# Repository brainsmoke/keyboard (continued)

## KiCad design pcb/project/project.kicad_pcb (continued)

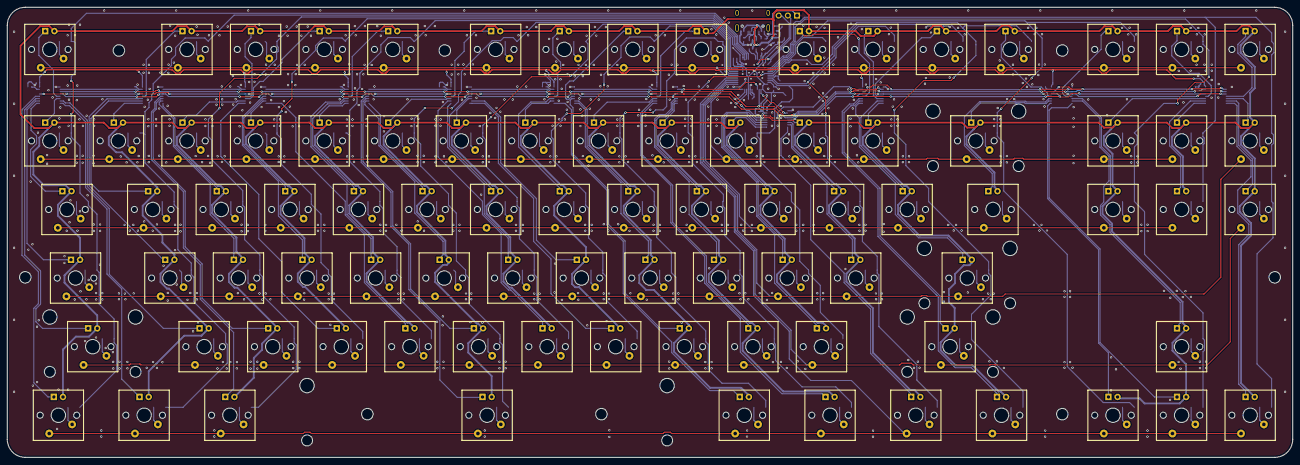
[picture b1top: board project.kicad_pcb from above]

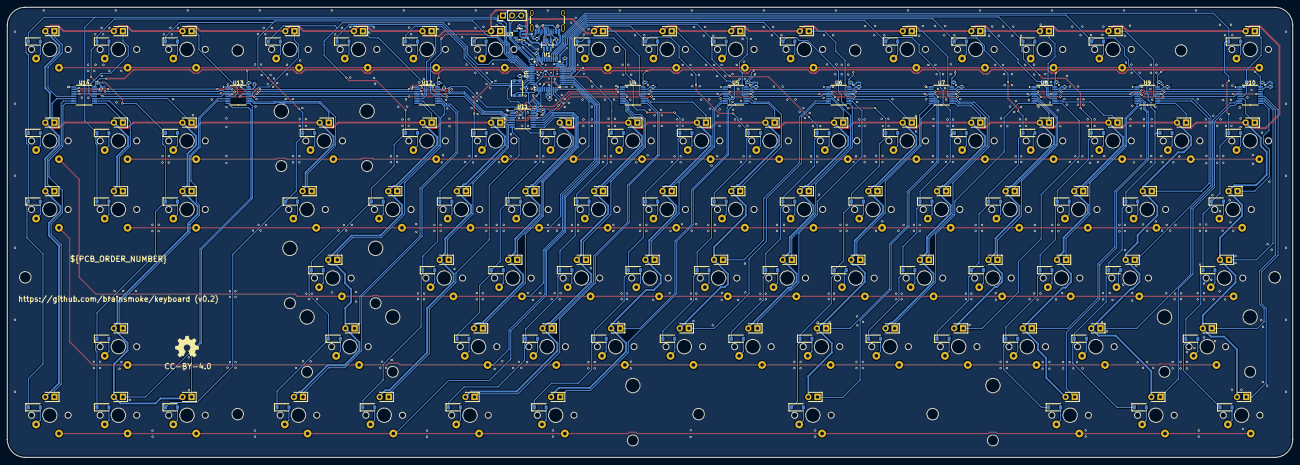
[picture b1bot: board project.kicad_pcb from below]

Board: 2 copper layers, 357.0 x 125.0 mm, 310 parts (223 on the bottom side), 234 nets.

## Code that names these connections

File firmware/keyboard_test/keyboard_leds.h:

#ifndef BITBANG_H
#define BITBANG_H

/* platform constants */

#define GPIO_ODR_OFFSET (0x14)
#define GPIO_BSRR_OFFSET (0x18)
#define GPIO_BRR_OFFSET (0x28)

/* GPIO, BSRR */

#define CLEAR(X) (X<<16)
#define SET(X)   (X)

/* GPIO C */
#define PIN_DATA_LEFT          (15)
#define PIN_DATA_RIGHT         (13)
#define PIN_CLK                (14)

/* GPIO A */
#define PIN_LATCH              (0)
#define PIN_NOT_OUTPUT_ENABLE  (1)


#define BIT_DATA_LEFT          (1<<PIN_DATA_LEFT)
#define BIT_DATA_RIGHT         (1<<PIN_DATA_RIGHT)
#define BIT_CLK                (1<<PIN_CLK)
#define BIT_LATCH              (1<<PIN_LATCH)
#define BIT_NOT_OUTPUT_ENABLE  (1<<PIN_NOT_OUTPUT_ENABLE)

#define MASK_CLK (BIT_CLK)
#define MASK_DATA (BIT_DATA_LEFT|BIT_DATA_RIGHT)

#ifndef __ASSEMBLER__

#include <stdint.h>
#include "config.h"

#define GPIO_LEDS_DATA (GPIOC)
#define GPIO_LEDS_LATCH (GPIOA)

#define BUFFER_BIT_DATA_LEFT (BIT_DATA_LEFT>>8)
#define BUFFER_BIT_DATA_RIGHT (BIT_DATA_RIGHT>>8)


#define MAX_BITS_PER_CHANNEL (56)
#define CHANNEL_PINS { BIT_DATA_LEFT, BIT_DATA_RIGHT, 0 }
#define CHANNEL_SIZES { 56, 32, 0 }

/* sends 56x bits parallel at 1/8th the clockspeed
 * gpio is the GPIO base address
 * 
 * probably close to 500 cycles including call
 */
void bitbang_56bits_stm32(uint8_t *buffer, volatile uint32_t *gpio_data_clock, volatile uint32_t *gpio_latch_enable, uint32_t not_enable_mask);
void write_wait_write(volatile uint32_t *addr, uint32_t pre_data, uint32_t post_data, uint32_t cycles);

#endif

#endif // BITBANG_H

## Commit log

2025-05-30 generate schematic
2025-05-31 board positioning
2025-05-31 put generator in scripts dir
2025-06-01 blagh
2025-06-07 routing done
2025-06-07 make external dimensions metric
2025-06-07 add build files
2025-06-07 add readme
2025-06-19 fixed the slots in the USB-C footprint, no clue how they got changed
2025-06-25 add measurement to keyboard key 'origin'
2025-06-25 add libopencm3 submodule
2025-06-25 copy common dir from usb_proto
2025-06-25 move files around
2025-06-25 test program
2025-06-26 reorg pcb/schematice generator scripts
2025-06-26 remove old file
2025-06-26 oops, missing file
2025-06-26 initial led driver code
2025-06-27 add header gen
2025-06-27 backlight test
2025-06-27 reshuffle
2025-06-27 clean up leds test
2025-06-28 rename binary
2025-06-30 test keyboard matrix hardware
2025-06-30 rename sheet labels to port names
2025-07-01 make key scanning slightly faster
2025-07-01 fix debug messgage
2025-07-17 add codegen scripts
2025-07-17 add distance calculation
2025-07-17 add codegen code
2026-02-15 rename headers
2026-02-15 add gitignore
2026-02-15 add footprints
2026-02-15 improve .gitignore
2026-02-15 add n-key rollover descriptor
2026-02-18 whitespace
2026-02-18 fix unfinished code to support unassigned keys
2026-02-25 working basic keyboard
2026-02-26 fix led mapping
2026-02-26 implement keyboard control protocol
2026-02-26 fix backlight
2026-02-26 add swapfn option to config.h
2026-02-26 fix led distance table
2026-03-01 implement set_idle ( untested :-E )
2026-03-01 don't send unneeded updates when fn is pressed
2026-03-04 save some RAM
2026-03-12 correct copyright date
2026-03-12 implement usb_hid_keyboard_key_is_down
2026-03-12 move/unify backlight leds bitbang routine
2026-03-12 remove unused files
2026-03-12 remove unused includes
2026-03-12 reorder functions for readability
2026-03-21 add laser cut 'case'
2026-03-22 improve keyboard cover
2026-03-24 add 'case'
2026-03-25 add photo of the finished project
2026-03-25 add todo
2026-03-25 fix img link
2026-03-27 add some more non-plated holes for version 0.2
2026-03-29 caps/scrollock indicator always at full brightness
2026-03-31 adjust backlight brightness
2026-04-01 hid descriptor decompilation
2026-04-01 automate pcba production files [untested]
2026-04-01 do correction processing in kicad coordinates
2026-04-06 tweak 3d-printed drill holes
2026-04-07 add extra holes to case (for v2)
2026-04-21 fix problems with lastercut case
2026-04-29 update Makefile
2026-04-29 rename Makefile variables
2026-04-29 add lasercut 'case'
2026-05-01 add photos
2026-05-17 add missing define in hid_keydef.h (not used in firmware)
